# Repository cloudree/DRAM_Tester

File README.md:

# DRAM_Tester
44256 / 4464 Dram Tester with Arduino

DRAM_Tester folder : KiCAD schematics and gerber files for arduino nano (or pro-mini)

DRAM_Testers : Arduino source

my blog posting (korean) :

https://blog.naver.com/cloudree/221388540394 

https://blog.naver.com/cloudree/221524164049

Good Luck!

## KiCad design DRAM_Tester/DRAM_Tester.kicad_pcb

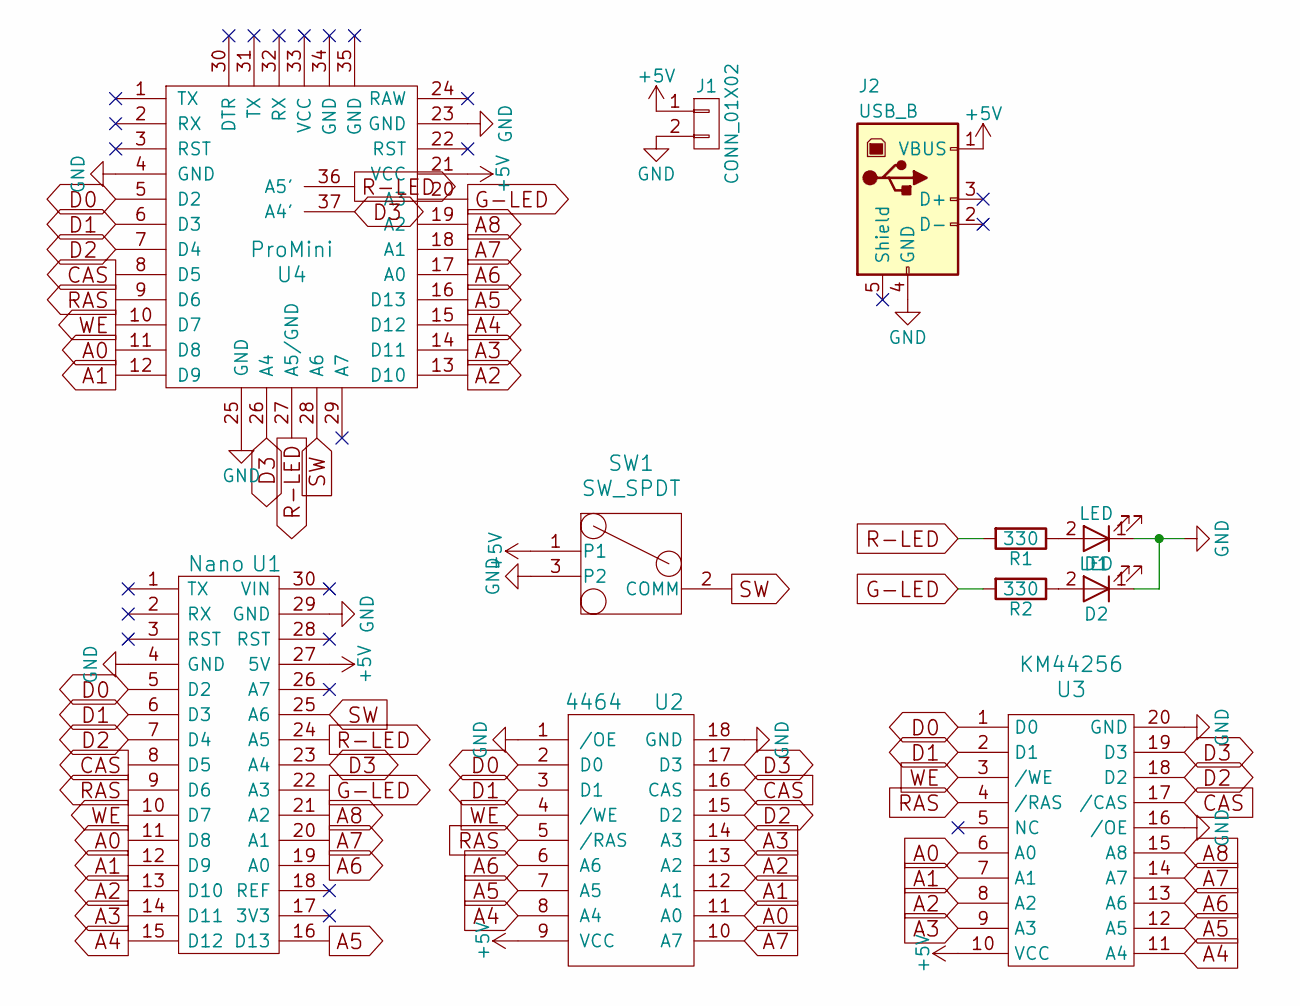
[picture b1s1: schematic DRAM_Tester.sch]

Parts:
D1, D2: LED; LED_Rectangular_W5.0mm_H2.0mm
J1: CONN_01X02; Pin_Header_Straight_1x02_Pitch2.54mm
J2: USB_B
R1, R2: 330; R_Axial_DIN0207_L6.3mm_D2.5mm_P10.16mm_Horizontal
SW1: SW_SPDT; Socket_Strip_Straight_1x03_Pitch2.54mm
U1: Nano; Arduino_Nano
U2: 4464; DIP-18_W7.62mm_Socket
U3: KM44256; DIP-20_W7.62mm_Socket
U4: ProMini; Arduino_Pro_Mini

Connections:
+5V: J1.1, J2.1 (VBUS), SW1.1, U1.27 (5V), U2.9 (VCC), U3.10 (VCC), U4.21 (VCC)
A0: U1.11 (D8), U2.11 (A0), U3.6 (A0), U4.11 (D8)
A1: U1.12 (D9), U2.12 (A1), U3.7 (A1), U4.12 (D9)
A2: U1.13 (D10), U2.13 (A2), U3.8 (A2), U4.13 (D10)
A3: U1.14 (D11), U2.14 (A3), U3.9 (A3), U4.14 (D11)
A4: U1.15 (D12), U2.8 (A4), U3.11 (A4), U4.15 (D12)
A5: U1.16 (D13), U2.7 (A5), U3.12 (A5), U4.16 (D13)
A6: U1.19 (A0), U2.6 (A6), U3.13 (A6), U4.17 (A0)
A7: U1.20 (A1), U2.10 (A7), U3.14 (A7), U4.18 (A1)
A8: U1.21 (A2), U3.15 (A8), U4.19 (A2)
CAS: U1.8 (D5), U2.16 (CAS), U3.17 (/CAS), U4.8 (D5)
D0: U1.5 (D2), U2.2 (D0), U3.1 (D0), U4.5 (D2)
D1: U1.6 (D3), U2.3 (D1), U3.2 (D1), U4.6 (D3)
D2: U1.7 (D4), U2.15 (D2), U3.18 (D2), U4.7 (D4)
D3: U1.23 (A4), U2.17 (D3), U3.19 (D3), U4.26 (A4), U4.37 (A4')
G-LED: R2.2, U1.22 (A3), U4.20 (A3)
GND: D1.1 (K), D2.1 (K), J1.2, J2.4 (GND), SW1.3 (P2), U1.4 (GND), U1.29 (GND), U2.1 (/OE), U2.18 (GND), U3.16 (/OE), U3.20 (GND), U4.4 (GND), U4.23 (GND), U4.25 (GND)
unnamed: D1.2 (A), R1.1
unnamed: D2.2 (A), R2.1
R-LED: R1.2, U1.24 (A5), U4.27 (A5/GND), U4.36 (A5')
RAS: U1.9 (D6), U2.5 (/RAS), U3.4 (/RAS), U4.9 (D6)
SW: SW1.2 (COMM), U1.25 (A6), U4.28 (A6)
WE: U1.10 (D7), U2.4 (/WE), U3.3 (/WE), U4.10 (D7)

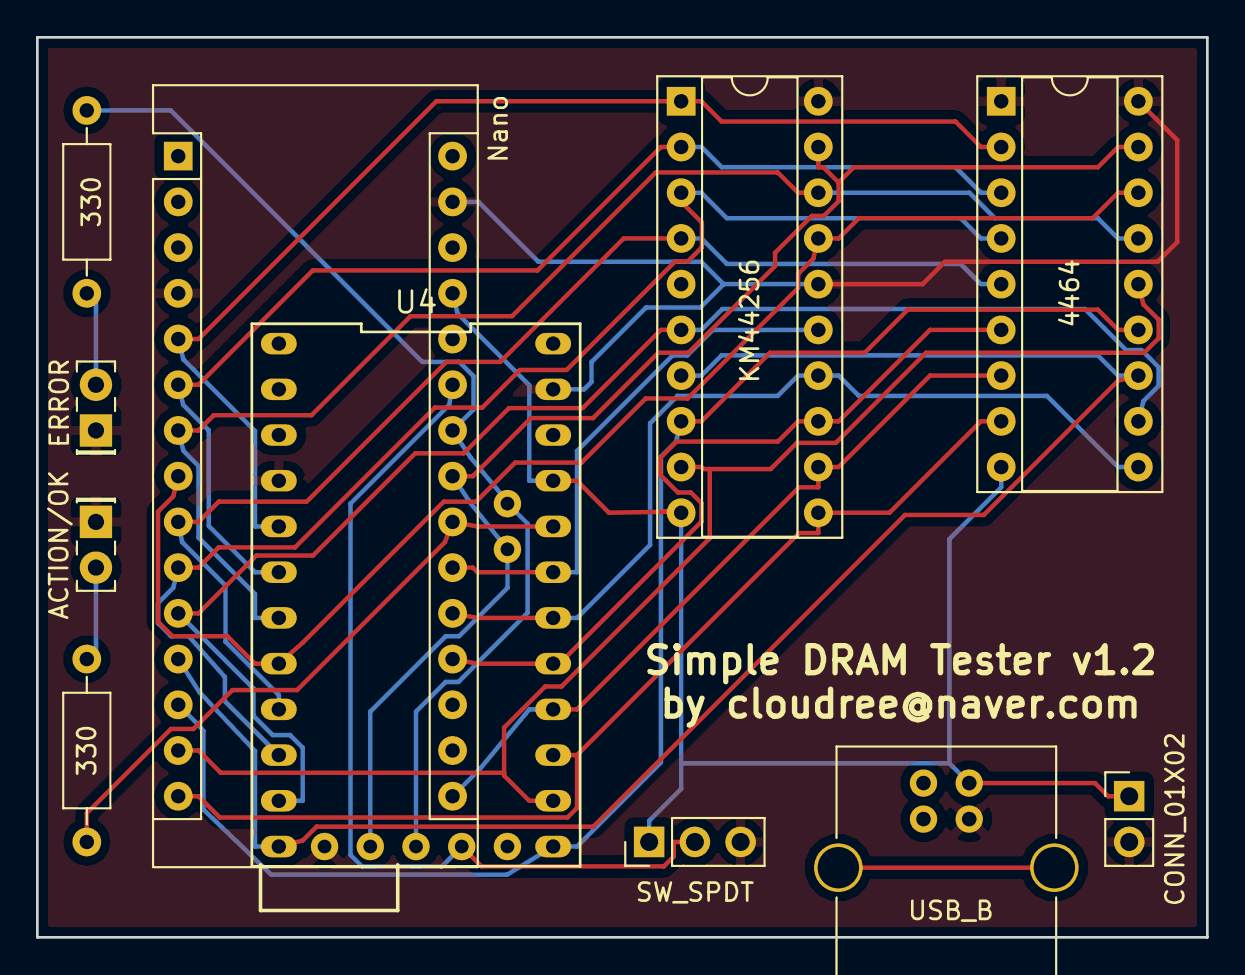
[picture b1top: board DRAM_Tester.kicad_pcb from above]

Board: 2 copper layers, 65.0 x 50.0 mm, 11 parts (0 on the bottom side), 23 nets.

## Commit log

2019-09-27 Arduino Sources (Nano)
2019-09-27 KiCad Schematics and Gerber files
2020-08-10 Update DRAM_Testers.ino
    Fixed Address range. thanks for Greg McCarthy<greg@gjmccarthy.co.uk>
